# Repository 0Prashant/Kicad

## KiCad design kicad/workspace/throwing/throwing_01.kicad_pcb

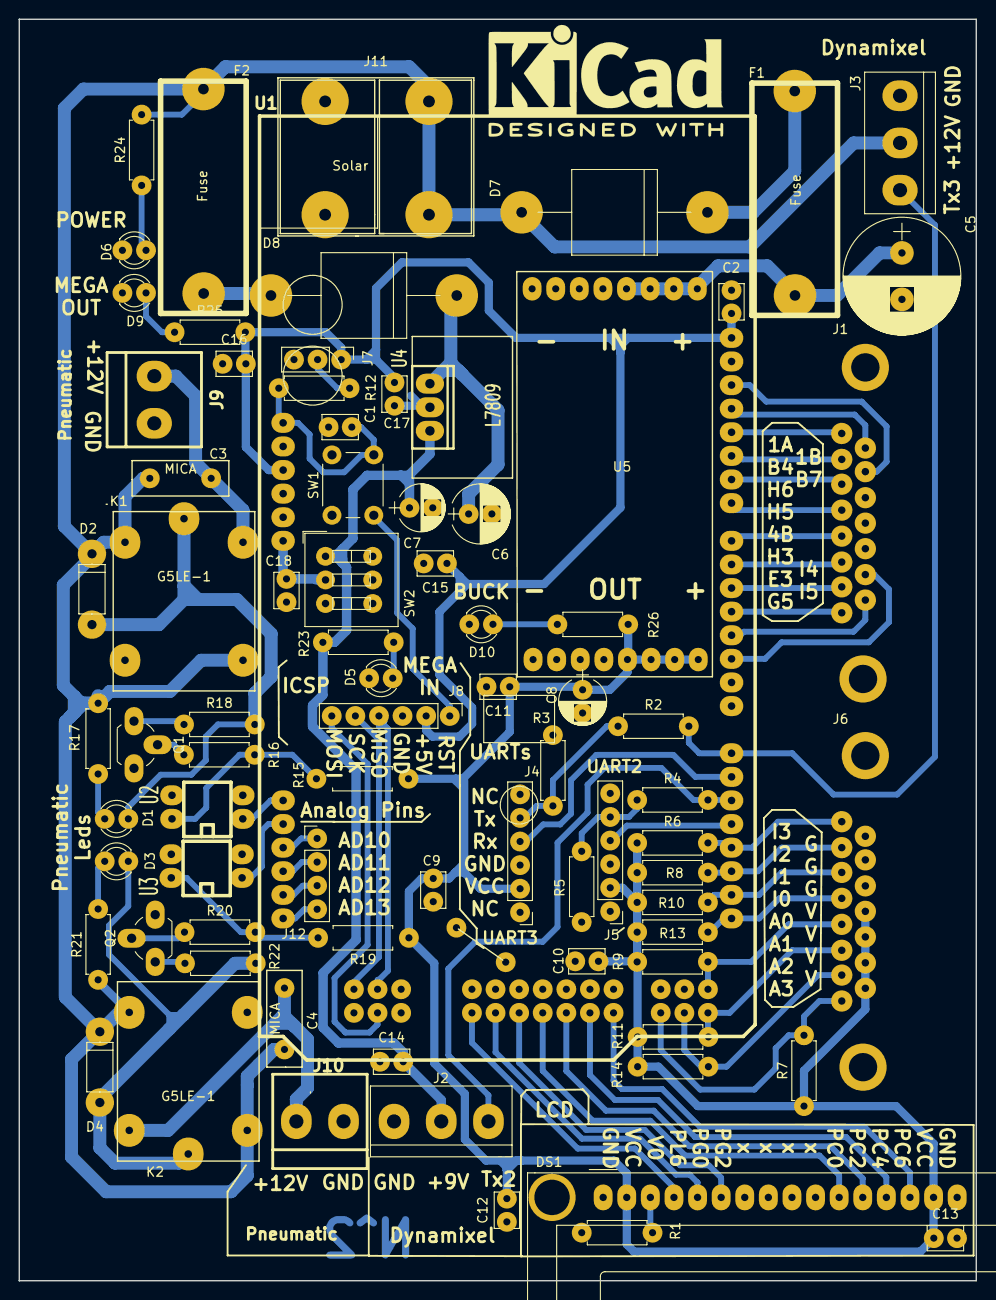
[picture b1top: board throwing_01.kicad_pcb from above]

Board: 2 copper layers, 103.0 x 135.8 mm, 81 parts (0 on the bottom side), 71 nets.

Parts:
C1, C2, C9, C10, C11, C12, C13, C14, C15, C16, C17, C18: 0.1uF; Cap_0.1in_pF
C3, C4: MICA; C-MICA
C5: 1000uF; Cao_1000uF
C6: 100uF; Cap_100uF
C7, C8: 10uF; Cap_10uF
D1, D3: LED; LED_D3.0mm
D2, D4: D; D_A-405_P7.62mm_Horizontal
D5: MEGA IN; LED_D3.0mm
D6: POWER; LED_D3.0mm
D7, D8: D; D_P600_R-6_P20.00mm_Horizontal
D9: MEGA OUT; LED_D3.0mm
D10: BUCK; LED_D3.0mm
DS1: LCD-16*2
F1, F2: Fuse; FUSE
J1: DB15_Female_Motor; DB15FC
J2: Dynamixel_09; bornier3
J3: Dynamixel_12; bornier3
J4: UART3; Socket_Strip_Straight_1x06_Pitch2.54mm
J5: UART2; Socket_Strip_Straight_1x06_Pitch2.54mm
J6: DB15_Female_Encoder; DB15FC
J7: RESET_PULL; Pin_Header_Straight_1x03_Pitch2.54mm
J8: ICSP; Pin_Header_Straight_1x06_Pitch2.54mm
J9, J10: Pneumatic; bornier2-medium
J11: Solar; SolarConn
J12: Conn_01x04_Male; Pin_Header_Straight_1x04_Pitch2.54mm
K1, K2: G5LE-1; Relay
Q1, Q2: BC547; _BC547
R1: 330; Res_Small
R2, R4: 1K; Res_Small
R3, R5: 2.2K; Res_Small
R6, R7, R8, R9, R10, R11, R12, R13, R14, R15, R19: 10K; Res_Small
R16, R20: 5K; Res_Small
R17, R21, R25, R26: 220; Res_Small
R18, R22, R24: 560; Res_Small
R23: 470; Res_Small
R27: R; Res_Small
SW1: SW_Push; SW_PUSH_6mm
SW2: SW_DIP_x01; SW_DIP_x3
U1: Arduino_Mega; ARDUINO_MEGA_SHIELD
U2, U3: FODM3011; dip_4
U4: L7809; LM78_heatsink
U5: LM2596-PSU

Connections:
+5V: C2.2, C15.1, C16.2, C17.1, J7.1, J8.2, R25.2, U1.5V, U1.AREF
+9V: C7.1, C14.2, J2.2, R23.2, SW2.1, U4.3
+12V: C3.1, C4.1, D2.1, D4.1, D7.2, F2.2, J3.2, J11.2, K1.3, K1.5, K2.3, K2.5, R17.1, R21.1, R24.2
/AD8: U1.AD8, U2.1
/AD9: U1.AD9, U3.1
/AD10: J12.1, U1.AD10
/AD11: J12.2, U1.AD11
/AD12: J12.3, U1.AD12
/AD13: J12.4, U1.AD13
/INT0: J6.4, R13.2, U1.21
/INT1: J6.3, R10.2, U1.20
/INT2: J6.2, R8.2, U1.19
/INT3: J6.1, R6.2, U1.18
/INT4: J1.14, U1.2
/INT5: J1.15, U1.3
/MISO: J8.4, U1.50
/MOSI: J8.6, U1.51
/OC1A: J1.1, U1.11
/OC1B: J1.9, U1.12
/OC4B: J1.5, U1.7
/PA0: J6.5, R9.2, U1.22
/PA1: J6.6, R11.2, U1.23
/PA3: J6.7, R14.2, U1.25
/PA5: J6.8, R7.2, U1.27
/PB4: J1.2, U1.10
/PB7: J1.10, U1.13
/PC0: DS1.11, U1.37
/PC2: DS1.12, U1.35
/PC4: DS1.13, U1.33
/PC6: DS1.14, U1.31
/PE3: J1.7, U1.5
/PG0: DS1.5, U1.41
/PG5: J1.8, U1.4
/PG6: DS1.6, U1.39
/PH3: J1.6, U1.6
/PH5: J1.4, U1.8
/PH6: J1.3, U1.9
/PL6: DS1.4, U1.43
/RESET: C1.1, J8.1, R12.2, SW1.2, U1.RST
/Rx2: J5.4, U1.17
/Rx3: J4.4, U1.15
/SCK: J8.5, U1.52
/Tx2: J2.3, R4.2, U1.16
/Tx3: J3.1, R2.2, U1.14
/Vin: C18.2, SW2.2, U1.V_IN
GND: C1.2, C2.1, C5.2, C6.2, C7.2, C8.2, C9.2, C10.1, C11.2, C12.1, C13.2, C14.1, C15.2, C16.1, C17.2, C18.1, D5.1, D6.1, D9.1, D10.1, DS1.1, DS1.16, J2.1, J3.3, J4.3, J5.3, J6.9, J6.10, J6.11, J7.3, J8.3, J9.2, J10.2, J11.1, Q1.3, Q2.3, R1.2, R3.2, R5.2, R27.1, R27.2, SW1.1, U1.GND1, U1.GND2, U1.GND3, U2.2, U2.3, U3.2, U3.3, U4.2, U5.2, U5.3
unnamed: C3.2, J9.1, K1.1
unnamed: C4.2, J10.1, K2.1
unnamed: C5.1, F1.1, U5.1
unnamed: C6.1, D8.1, U4.1
unnamed: D1.1, D2.2, K1.2, R18.2
unnamed: D1.2, R17.2
unnamed: D3.1, D4.2, K2.2, R22.1
unnamed: D3.2, R21.2
unnamed: D5.2, R23.1
unnamed: D6.2, R24.1
unnamed: D7.1, F1.2
unnamed: D8.2, F2.1
unnamed: D9.2, R25.1
unnamed: D10.2, R26.1
unnamed: DS1.3, R1.1
unnamed: J4.5, R2.1, R3.1
unnamed: J5.5, R4.1, R5.1
unnamed: J7.2, R12.1
unnamed: Q1.1, R18.1
unnamed: Q1.2, R16.1
unnamed: Q2.1, R22.2
unnamed: Q2.2, R20.1
unnamed: R15.2, R16.2, U2.4
unnamed: R19.2, R20.2, U3.4
VCC: C8.1, C9.1, C10.2, C11.1, C12.2, C13.1, DS1.2, DS1.15, J4.2, J5.2, J6.12, J6.13, J6.14, J6.15, R6.1, R7.1, R8.1, R9.1, R10.1, R11.1, R13.1, R14.1, R15.1, R19.1, R26.2, U5.4

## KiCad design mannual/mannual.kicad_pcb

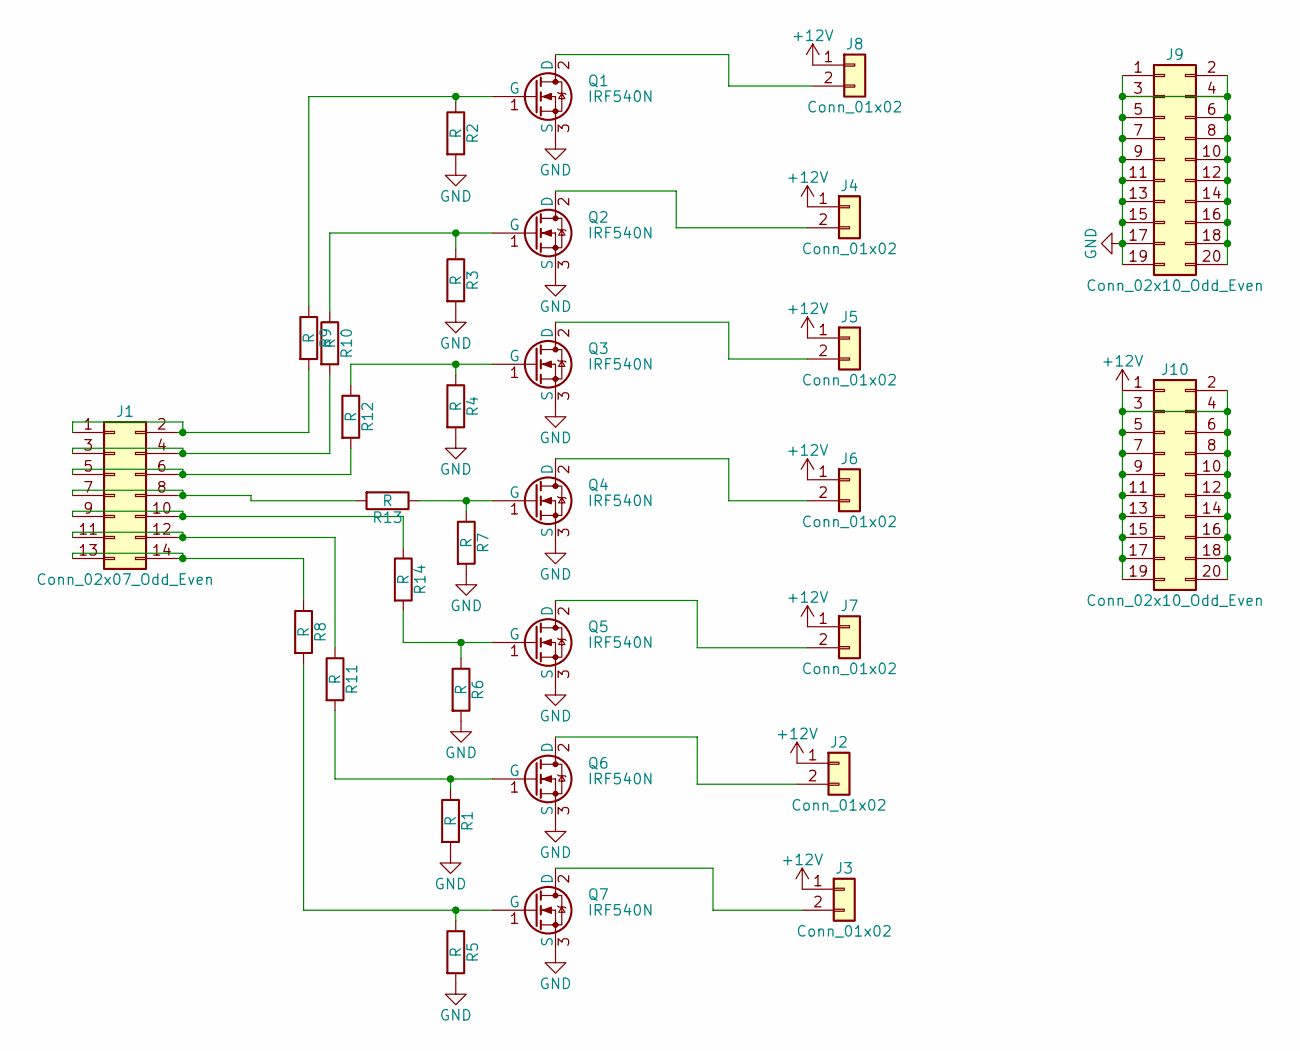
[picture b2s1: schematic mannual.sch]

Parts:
J1: Conn_02x07_Odd_Even; Pin_Header_Straight_2x07_Pitch2.54mm
J2, J3, J4, J5, J6, J7, J8: Conn_01x02; Connector_Bornier_2
J9, J10: Conn_02x10_Odd_Even; Pin_Header_Straight_2x10_Pitch2.54mm
Q1, Q2, Q3, Q4, Q5, Q6, Q7: IRF540N; Voltage_Regulators
R1, R2, R3, R4, R5, R6, R7: R; Resistor_small
R8, R9, R10, R11, R12, R13, R14: R; R_Axial_DIN0207_L6.3mm_D2.5mm_P2.54mm_Vertical

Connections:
+12V: J2.1, J3.1, J4.1, J5.1, J6.1, J7.1, J8.1, J10.1, J10.2, J10.3, J10.4, J10.5, J10.6, J10.7, J10.8, J10.9, J10.10, J10.11, J10.12, J10.13, J10.14, J10.15, J10.16, J10.17, J10.18, J10.19, J10.20
GND: J9.1, J9.2, J9.3, J9.4, J9.5, J9.6, J9.7, J9.8, J9.9, J9.10, J9.11, J9.12, J9.13, J9.14, J9.15, J9.16, J9.17, J9.18, J9.19, J9.20, Q1.3 (S), Q2.3 (S), Q3.3 (S), Q4.3 (S), Q5.3 (S), Q6.3 (S), Q7.3 (S), R1.2, R2.2, R3.2, R4.2, R5.2, R6.2, R7.2
unnamed: J1.1, J1.2, R9.2
unnamed: J1.3, J1.4, R10.2
unnamed: J1.5, J1.6, R12.2
unnamed: J1.7, J1.8, R13.2
unnamed: J1.9, J1.10, R14.1
unnamed: J1.11, J1.12, R11.1
unnamed: J1.13, J1.14, R8.1
unnamed: J2.2, Q6.2 (D)
unnamed: J3.2, Q7.2 (D)
unnamed: J4.2, Q2.2 (D)
unnamed: J5.2, Q3.2 (D)
unnamed: J6.2, Q4.2 (D)
unnamed: J7.2, Q5.2 (D)
unnamed: J8.2, Q1.2 (D)
unnamed: Q1.1 (G), R2.1, R9.1
unnamed: Q2.1 (G), R3.1, R10.1
unnamed: Q3.1 (G), R4.1, R12.1
unnamed: Q4.1 (G), R7.1, R13.1
unnamed: Q5.1 (G), R6.1, R14.2
unnamed: Q6.1 (G), R1.1, R11.2
unnamed: Q7.1 (G), R5.1, R8.2

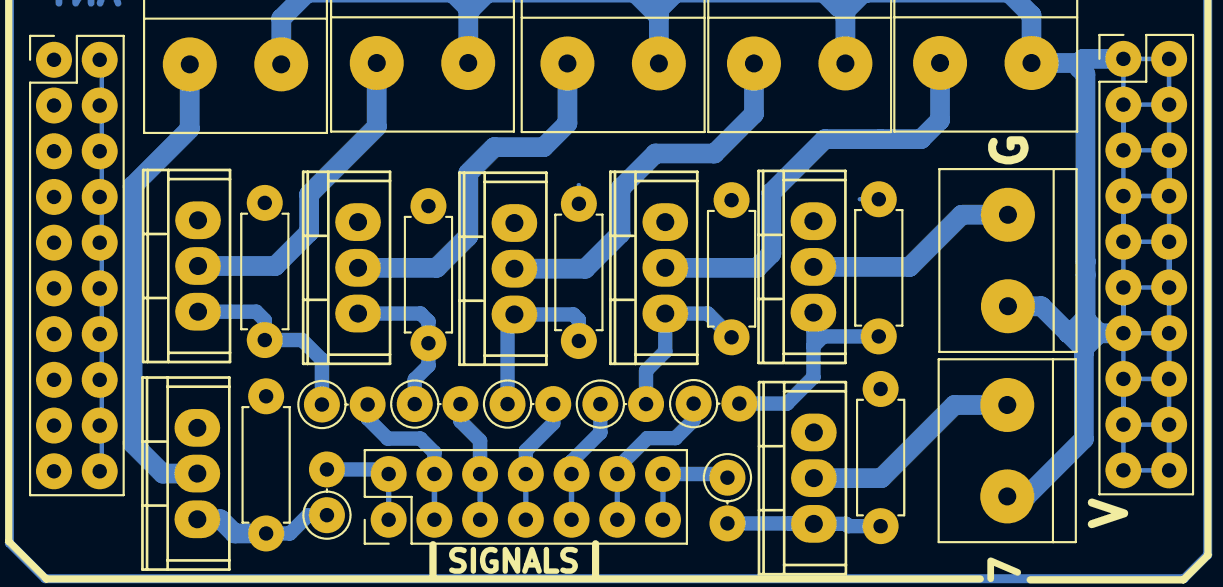
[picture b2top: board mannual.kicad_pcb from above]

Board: 2 copper layers, 31 parts (0 on the bottom side), 23 nets.

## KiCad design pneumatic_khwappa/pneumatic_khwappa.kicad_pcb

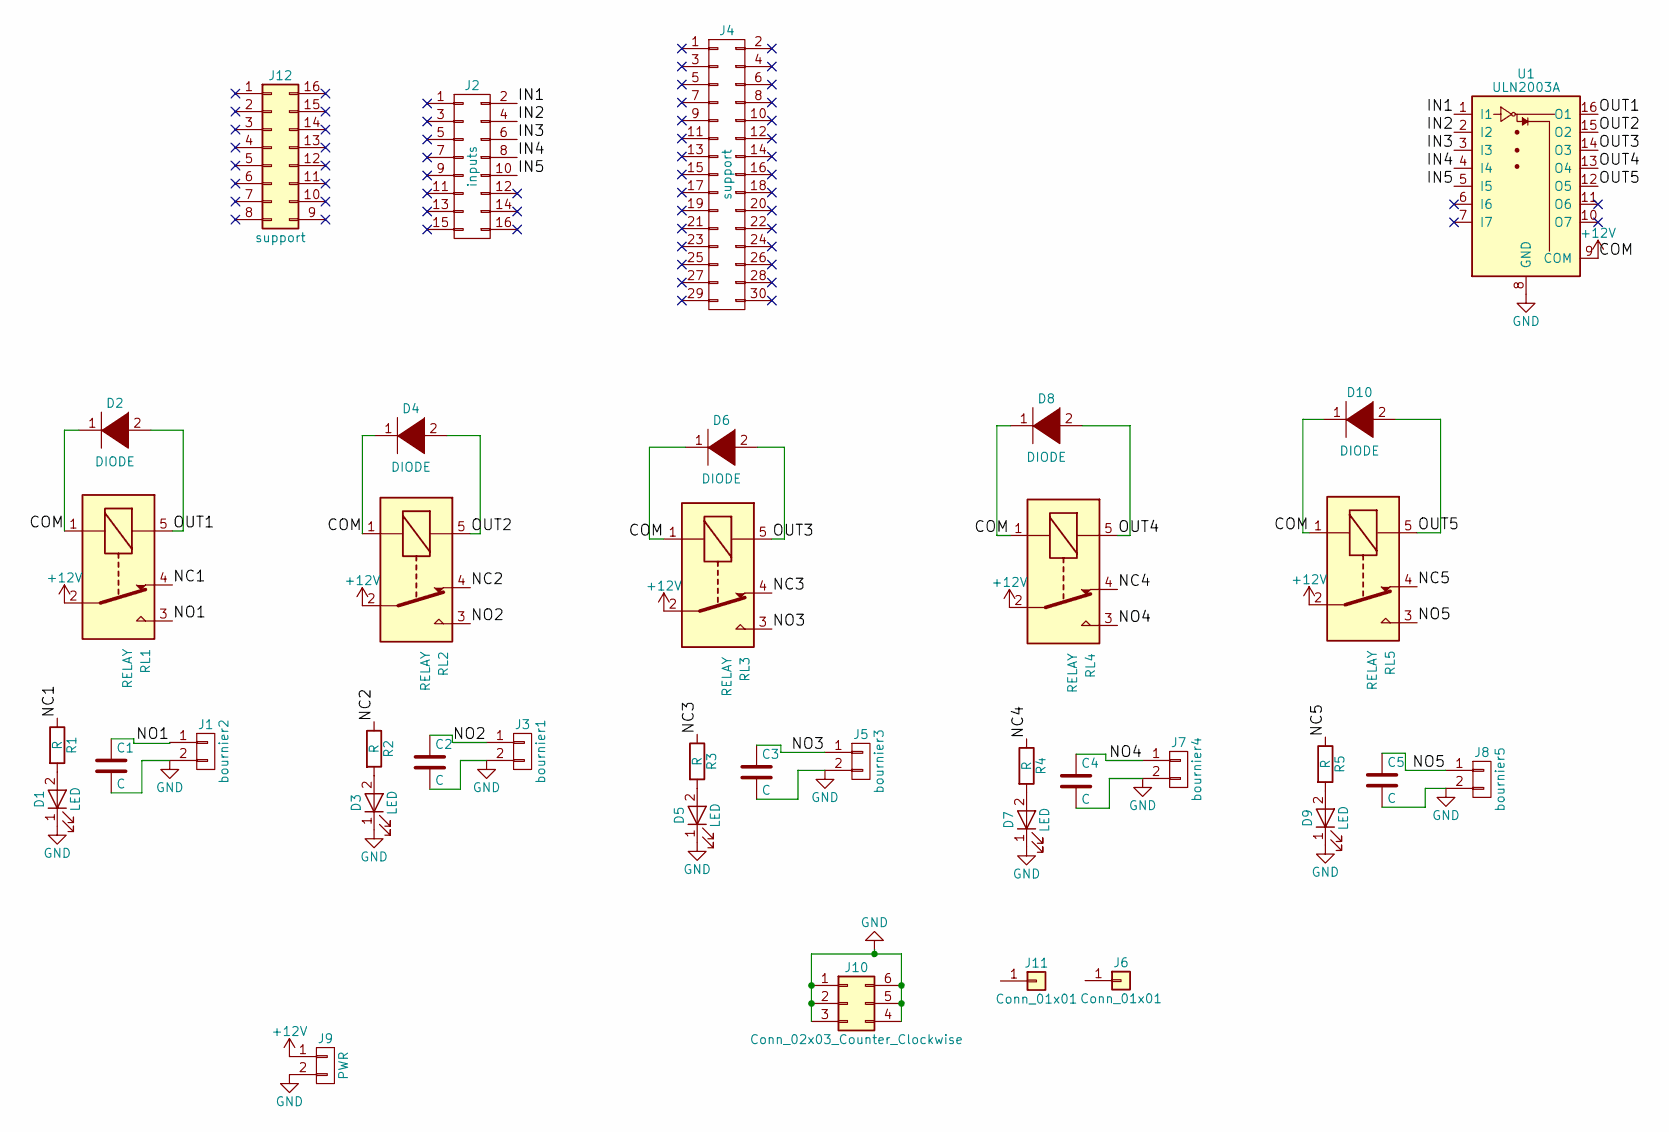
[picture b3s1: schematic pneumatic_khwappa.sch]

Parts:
C1, C2, C3, C4, C5: C; C_Rect_L7.0mm_W2.5mm_P5.00mm
D1, D3, D5, D7, D9: LED; LED_D3.0mm
D2, D4, D6, D8, D10: DIODE; D_DO-35_SOD27_P7.62mm_Horizontal
J1: bournier2; Bornier2
J2: inputs; Pin_Header_Straight_2x08_Pitch2.54mm
J3: bournier1; Bornier2
J4: support; Pin_Header_Straight_2x15_Pitch2.54mm
J5: bournier3; Bornier2
J6, J11: Conn_01x01; 1pin
J7: bournier4; Bornier2
J8: bournier5; Bornier2
J9: PWR; Solar_Connector
J10: Conn_02x03_Counter_Clockwise; Pin_Header_Straight_2x03_Pitch2.54mm
J12: support; Pin_Header_Straight_2x08_Pitch2.54mm
R1, R2, R3, R4, R5: R; R_Axial_DIN0204_L3.6mm_D1.6mm_P7.62mm_Horizontal
RL1, RL2, RL3, RL4, RL5: RELAY; Relay_6V
U1: ULN2003A; DIP-16_W7.62mm

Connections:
+12V: D2.1 (K), D4.1 (K), D6.1 (K), D8.1 (K), D10.1 (K), J9.1, RL1.1, RL1.2, RL2.1, RL2.2, RL3.1, RL3.2, RL4.1, RL4.2, RL5.1, RL5.2, U1.9 (COM)
/IN1: J2.2, U1.1 (I1)
/IN2: J2.4, U1.2 (I2)
/IN3: J2.6, U1.3 (I3)
/IN4: J2.8, U1.4 (I4)
/IN5: J2.10, U1.5 (I5)
/NC1: R1.1, RL1.4
/NC2: R2.1, RL2.4
/NC3: R3.1, RL3.4
/NC4: R4.1, RL4.4
/NC5: R5.1, RL5.4
/NO1: C1.1, J1.1, RL1.3
/NO2: C2.1, J3.1, RL2.3
/NO3: C3.1, J5.1, RL3.3
/NO4: C4.1, J7.1, RL4.3
/NO5: C5.1, J8.1, RL5.3
/OUT1: D2.2 (A), RL1.5, U1.16 (O1)
/OUT2: D4.2 (A), RL2.5, U1.15 (O2)
/OUT3: D6.2 (A), RL3.5, U1.14 (O3)
/OUT4: D8.2 (A), RL4.5, U1.13 (O4)
/OUT5: D10.2 (A), RL5.5, U1.12 (O5)
GND: C1.2, C2.2, C3.2, C4.2, C5.2, D1.1 (K), D3.1 (K), D5.1 (K), D7.1 (K), D9.1 (K), J1.2, J3.2, J5.2, J7.2, J8.2, J9.2, J10.1, J10.2, J10.3, J10.4, J10.5, J10.6, U1.8 (GND)
unnamed: D1.2 (A), R1.2
unnamed: D3.2 (A), R2.2
unnamed: D5.2 (A), R3.2
unnamed: D7.2 (A), R4.2
unnamed: D9.2 (A), R5.2

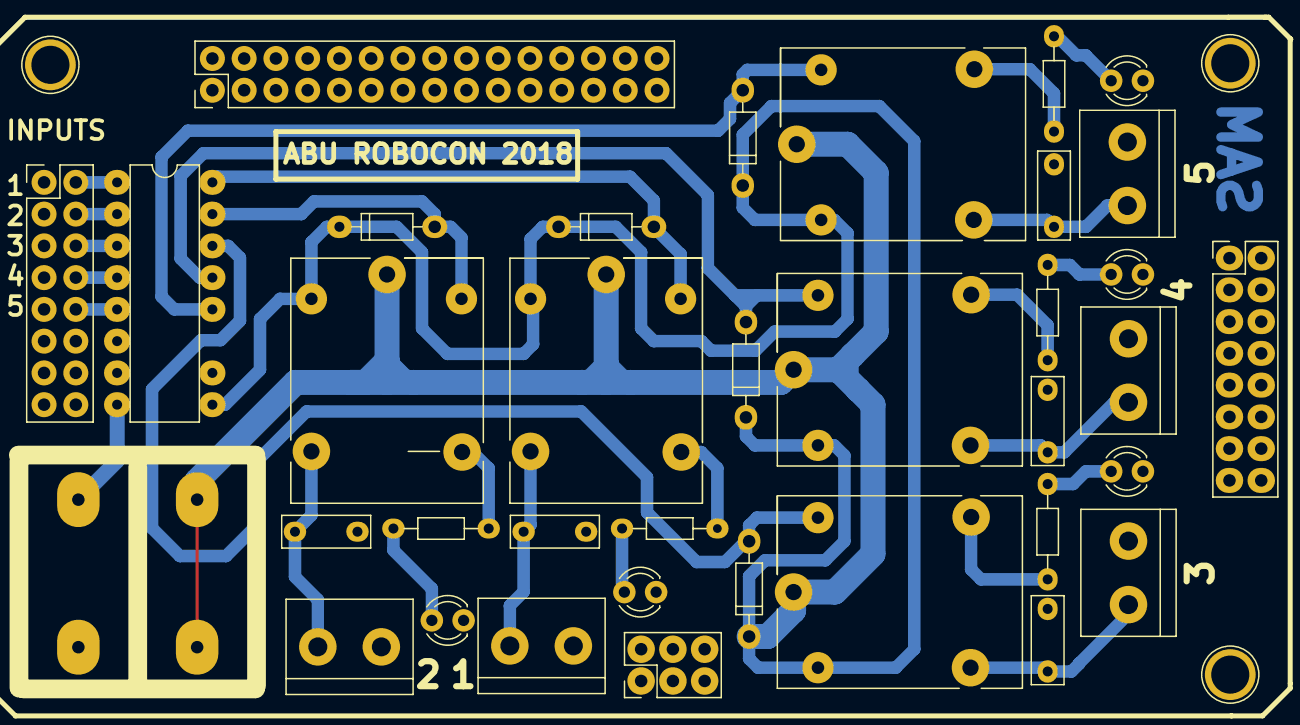
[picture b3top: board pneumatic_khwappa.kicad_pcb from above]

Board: 2 copper layers, 39 parts (0 on the bottom side), 27 nets.

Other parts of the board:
J11#2: Conn_01x01; 1pin
